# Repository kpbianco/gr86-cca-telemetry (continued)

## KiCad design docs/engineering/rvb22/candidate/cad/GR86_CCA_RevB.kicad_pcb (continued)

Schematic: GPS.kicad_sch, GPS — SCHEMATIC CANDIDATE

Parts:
C401, C402: 22u /25V X7R 10%; C_1210_3225Metric; MPN MCAST32MSB7226KPNA01; LCSC C5372271
C403, C404, C405: 100n /50V X7R; C_0603_1608Metric; MPN GCM188R71H104KA57D; LCSC C85864
D401: SEARCH (blink / no fix); LED_0603_1608Metric; MPN APT1608SGC; LCSC C5875754
D402: TPD1E05U06DPYR; TI_DPY0002A_TPD1E05U06_SMDMask; MPN TPD1E05U06DPYR; LCSC C436349
J401: U.FL-R-SMT-1(80); Hirose_UFL_R_SMT_1_80_RevB; MPN U.FL-R-SMT-1(80); LCSC C88374
L406: 1.6nH 5% RF MATCH; Murata_LQW18AS_1608; MPN LQW18AS1N6J0ZD
R401: 0R GPS ISOLATION; R_0603_1608Metric; MPN CRCW06030000Z0EA; LCSC C844915
R402, R403, R404: 220R; R_0603_1608Metric; MPN AA0603FR-07220RL; LCSC C2100485
R405: 1k; R_0603_1608Metric; MPN CRCW06031K00FKEA; LCSC C844920
R407, R408, R409: 100k; R_0603_1608Metric; MPN CRCW0603100KFKEA; LCSC C844916
R410: 10k /UART idle; R_0603_1608Metric; MPN CRCW060310K0FKEA; LCSC C844918
R411: 100k /off-state; R_0603_1608Metric; MPN CRCW0603100KFKEA; LCSC C844916
TP401: TP_GPS_TX; TestPoint_Pad_D1.5mm; MPN BARE PCB PAD
TP402: TP_GPS_RX; TestPoint_Pad_D1.5mm; MPN BARE PCB PAD
TP403: TP_GPS_PPS; TestPoint_Pad_D1.5mm; MPN BARE PCB PAD
TP404: TP_GPS_3V3; TestPoint_Pad_D1.5mm; MPN BARE PCB PAD
TP405: TP_GPS_GND; TestPoint_Pad_D1.5mm; MPN BARE PCB PAD
U401: PA1616D; CDTop_PA1616D_20Pad_v06; MPN PA1616D
U402, U404: SN74LVC2G125DCUR; VSSOP-8_2.3x2mm_P0.5mm; MPN SN74LVC2G125DCUR; LCSC C21404
U403: MIC5504-3.3YM5-TR; SOT-23-5; MPN MIC5504-3.3YM5-TR; LCSC C88419

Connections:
+3V3: C404.1, R410.1, U402.8 (VCC); also elsewhere on the board
+5V: R401.1; also elsewhere on the board
GND: C401.2, C402.2, C403.2, C404.2, C405.2, D401.1 (K), D402.2 (GND_A), J401.2 (Ext), R407.2, R408.2, R409.2, R411.2, TP405.1, U401.3 (GND), U401.8 (GND), U401.12 (GND), U401.19 (GND), U402.1 (1OE_N), U402.4 (GND), U402.7 (2OE_N), U403.2 (GND), U404.1 (1OE_N), U404.4 (GND), U404.7 (2OE_N); also elsewhere on the board
GPS_3V3: C402.1, C403.1, C405.1, TP404.1, U401.1 (VCC), U403.5 (VOUT), U404.8 (VCC)
GPS_5V_IN: C401.1, R401.2, U403.1 (VIN), U403.3 (EN)
GPS_ANT_RF_BIASED: L406.1, U401.11 (EX_ANT_BIASED)
GPS_EXT_ANT: D402.1 (IO_K), J401.1 (In), L406.2
GPS_FIX_RAW: R409.1, U401.5 (3D_FIX), U404.5 (2A)
GPS_PPS_BUFFER: R403.1, U402.3 (2Y)
GPS_PPS_MCU: R403.2; also elsewhere on the board
GPS_PPS_RAW: R408.1, TP403.1, U401.13 (PPS_2V8), U402.5 (2A)
GPS_RX_BUFFER: R404.1, U404.6 (1Y)
GPS_RX_MODULE: R404.2, TP402.1, U401.10 (RX0)
GPS_SEARCH_BUFFER: R405.1, U404.3 (2Y)
GPS_SEARCH_LED_A: D401.2 (A), R405.2
GPS_TX_BUFFER: R402.1, U402.6 (1Y)
GPS_TX_MCU: R410.2, R411.1, U404.2 (1A); also elsewhere on the board
GPS_TX_MODULE_BUFFERED: R402.2; also elsewhere on the board
GPS_TX_RAW: R407.1, TP401.1, U401.9 (TX0), U402.2 (1A)

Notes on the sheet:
RVB-05 GPS — TX/RX CROSSED; LEVEL BUFFERS; DEDICATED3.3V PA1616D pin1 is upper-left in the manufacturer top view. No electrical pad21.
U402 receives GPS TX/PPS on main3V3; U404 drives GPS RX on GPS3V3. Exact TI input VIH2.0V. R410/R411 set GPIO17 UART idle; GPIO17 may drive LOW briefly at power-up, so firmware renegotiates after boot. GPS-only fixture:1k bleed on main3V3, verify main rail<=0.2V before asserting off-domain behavior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
UART default and external-antenna ESD

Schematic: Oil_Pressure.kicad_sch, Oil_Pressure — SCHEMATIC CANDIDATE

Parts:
C501, C513, C523: 22n /50V X7R; C_0603_1608Metric; MPN CGA3E2X7R1H223K080AE; LCSC C2176922
C502, C531: 100n /50V X7R; C_0603_1608Metric; MPN GCM188R71H104KA57D; LCSC C85864
C503: 100n /100V X7R; C_0805_2012Metric; MPN CGA4J2X7R2A104K125AA; LCSC C342919
C504, C505, C506: 10u /50V X7R; KEMET_C1210_10u50V; MPN C1210C106K5RACTU; LCSC C2167688
C511, C512, C521, C522: 1u /16V X7R; C_0603_1608Metric; MPN GCM188R71C105KA64D; LCSC C161212
C514, C524: 100p /50V C0G5%; C_0603_1608Metric; MPN CGA3E2C0G1H101J080AA; LCSC C76709
C532: 10n /50V C0G 5% OUT HF; C_0603_1608Metric; MPN GRM1885C1H103JA01D
D501: ESD2CAN24DBZRQ1; SOT-23; MPN ESD2CAN24DBZRQ1; LCSC C5736151
D502: SS16 /60V Schottky; D_SMA; MPN SS16HE3_B/H; LCSC C266798
D511, D512, D521, D522: PMEG2010BEA,115; Nexperia_SOD323_PMEG2010BEA; MPN PMEG2010BEA,115; LCSC C455041
R501: 27.4k /0.1%; R_0603_1608Metric; MPN TNPW060327K4BEEA; LCSC C2079063
R502, R504: 10k /0.1%; R_0603_1608Metric; MPN TNPW060310K0BEEA; LCSC C844890
R503: 36.5k /0.1%; R_0603_1608Metric; MPN TNPW060336K5BEEA; LCSC C2089518
R505: 118k /0.1%; R_0805_2012Metric; MPN TNPW0805118KBEEA; LCSC C1709453
R506: 100k; R_0603_1608Metric; MPN CRCW0603100KFKEA; LCSC C844916
R507: 4.7R /1% pulse HP; R_2512_6332Metric; MPN CRCW25124R70FKEGHP; LCSC C2075852
R511, R521: 1M /0.1%; R_0805_2012Metric; MPN TNPW08051M00BEEA; LCSC C844679
R512, R522: 4.02k /0.1%; R_0603_1608Metric; MPN TNPW06034K02BEEA; LCSC C844459
R513, R523: 124k /0.1%; R_0805_2012Metric; MPN TNPW0805124KBEEA; LCSC C1709494
R514, R524: 1k /0.1%; R_0603_1608Metric; MPN TNPW06031K00BEEA; LCSC C844891
R515, R525: 220R /1%150ppm; R_0603_1608Metric; MPN AA0603FR-07220RL; LCSC C2100485
TP501: TP_OIL_SIG; TestPoint_Pad_D1.5mm; MPN BARE PCB PAD
TP502: TP_OIL_FILTERED; TestPoint_Pad_D1.5mm; MPN BARE PCB PAD
TP503: TP_ADC_NODE; TestPoint_Pad_D1.5mm; MPN BARE PCB PAD
TP504: TP_OIL_GND; TestPoint_Pad_D1.5mm; MPN BARE PCB PAD
TP505: TP_OIL_5V; TestPoint_Pad_D1.5mm; MPN BARE PCB PAD
TP506: TP_OIL_EXC_ADC; TestPoint_Pad_D1.5mm; MPN BARE PCB PAD
TP507: TP_OIL_SHDN; TestPoint_Pad_D1.5mm; MPN BARE PCB PAD
TP508: TP_OIL_POWER_FAULT; TestPoint_Pad_D1.5mm; MPN BARE PCB PAD
TP509: TP_OIL_EFUSE_RTN; TestPoint_Pad_D1.5mm; MPN BARE PCB PAD
TP510: TP_OIL_EFUSE_OUT; TestPoint_Pad_D1.5mm; MPN BARE PCB PAD
U501: TPS26600PWPR; TI_PWP0016A_TPS2660; MPN TPS26600PWPR; LCSC C544399
U502: OPA2333AIDR; SOIC-8_3.9x4.9mm_P1.27mm; MPN OPA2333AIDR; LCSC C38732

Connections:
+3V3: C531.1, D511.1 (K), D521.1 (K), R506.1, U502.8 (VPOS); also elsewhere on the board
+5V: C502.1, R501.1, R503.1, U501.1 (IN1), U501.2 (IN2); also elsewhere on the board
ADC_NODE: C513.1, D511.2 (A), D512.1 (K), R513.1, R515.2, TP503.1; also elsewhere on the board
GND: C502.2, C503.2, C504.2, C505.2, C506.2, C511.2, C512.2, C513.2, C521.2, C522.2, C523.2, C531.2, C532.2, D501.3 (GND), D502.2 (A), D512.2 (A), D522.2 (A), R512.2, R514.2, R522.2, R524.2, TP504.1, U501.9 (GND), U502.4 (VNEG); also elsewhere on the board
OIL_5V: C503.1, D501.2 (IO2), R507.2, R521.1, TP505.1; also elsewhere on the board
OIL_AMP_OUT: C514.1, R515.1, U502.1 (OUT_A)
OIL_DVDT: C501.1, U501.12 (DVDT)
OIL_EFUSE_OUT: C504.1, C505.1, C506.1, C532.1, D502.1 (K), R507.1, TP510.1, U501.15 (OUT1), U501.16 (OUT2)
OIL_EFUSE_RTN: C501.2, R502.2, R504.2, R505.2, TP509.1, U501.8 (RTN), U501.17 (EP_RTN)
OIL_EXCITATION_ADC: C523.1, D521.2 (A), D522.1 (K), R523.1, R525.2, TP506.1; also elsewhere on the board
OIL_EXC_AMP_OUT: C524.1, R525.1, U502.7 (OUT_B)
OIL_EXC_FB: C524.2, R523.2, R524.1, U502.6 (INB_N)
OIL_EXC_FILTERED: C521.1, C522.1, R521.2, R522.1, U502.5 (INB_P)
OIL_FB: C514.2, R513.2, R514.1, U502.2 (INA_N)
OIL_FILTERED: C511.1, C512.1, R511.2, R512.1, TP502.1, U502.3 (INA_P)
OIL_ILIM: R505.1, U501.11 (ILIM)
OIL_OVP: R503.2, R504.1, U501.5 (OVP)
OIL_POWER_FAULT_N: R506.2, TP508.1, U501.14 (FLT_N)
OIL_SHDN: TP507.1, U501.7 (SHDN)
OIL_SIG: D501.1 (IO1), R511.1, TP501.1; also elsewhere on the board
OIL_UVLO: R501.2, R502.1, U501.3 (UVLO)

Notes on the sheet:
RVB-06 — HONEYWELL150psi /RATIOMETRIC5V /GPIO1 ADC Connector signal → 1:249.76 attenuator → precision gain125 → low-impedance ADC drive. OIL5V excitation is current limited and reverse-current blocked; no direct5V-to-ADC path.
RTN is a private eFuse reference; do not short it to GND. Its thermal pad also goes to RTN. MODE floats for circuit-breaker/auto-retry. SHDN uses its internal2–3.4V pullup; TP permits temporary low-to-RTN reset. UVLO is externally programmed: grounding it would select a14.9V default and disable a5V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
RVB22 C532 OUT-to-GND HF bypass:10nF C0G50V; never privateRTN. Direct U501 OUTpad16 feed also joins C504 OUTland and existing In1 OUTcopper; use actual non-tree nodal model. Preserve C504/C505/C506 bulk and C514 feedback. New-loop25nH/common-star10nH are allocations; native fill and hardware remain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

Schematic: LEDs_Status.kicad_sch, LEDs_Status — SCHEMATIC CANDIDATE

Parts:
D601: PWR; LED_0603_1608Metric; MPN APT1608SGC; LCSC C5875754
D602: BLE; LED_0603_1608Metric; MPN APT1608SGC; LCSC C5875754
D603: CAN; LED_0603_1608Metric; MPN APT1608SGC; LCSC C5875754
D604: GPS; LED_0603_1608Metric; MPN APT1608SGC; LCSC C5875754
D605: SYS; LED_0603_1608Metric; MPN APT1608SGC; LCSC C5875754
D606: OIL; LED_0603_1608Metric; MPN APT1608SGC; LCSC C5875754
R601: 1k / GPIO15; R_0603_1608Metric; MPN CRCW06031K00FKEA; LCSC C844920
R602: 1k / GPIO6; R_0603_1608Metric; MPN CRCW06031K00FKEA; LCSC C844920
R603: 1k / GPIO7; R_0603_1608Metric; MPN CRCW06031K00FKEA; LCSC C844920
R604: 1k / GPIO8; R_0603_1608Metric; MPN CRCW06031K00FKEA; LCSC C844920
R605: 1k / GPIO10; R_0603_1608Metric; MPN CRCW06031K00FKEA; LCSC C844920
R606: 1k / GPIO9; R_0603_1608Metric; MPN CRCW06031K00FKEA; LCSC C844920

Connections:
GND: D601.1 (K), D602.1 (K), D603.1 (K), D604.1 (K), D605.1 (K), D606.1 (K); also elsewhere on the board
LED_BLE: R602.1; also elsewhere on the board
LED_BLE_A: D602.2 (A), R602.2
LED_CAN: R603.1; also elsewhere on the board
LED_CAN_A: D603.2 (A), R603.2
LED_GPS: R604.1; also elsewhere on the board
LED_GPS_A: D604.2 (A), R604.2
LED_OIL: R606.1; also elsewhere on the board
LED_OIL_A: D606.2 (A), R606.2
LED_PWR: R601.1; also elsewhere on the board
LED_PWR_A: D601.2 (A), R601.2
LED_SYS: R605.1; also elsewhere on the board
LED_SYS_A: D605.2 (A), R605.2

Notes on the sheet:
STATUS INDICATORS — ACTIVE HIGH GPIO3/GPIO46 strapping pins are free of external LED loads in Rev B. Firmware Rev B contract moves OIL to GPIO9 and PWR to GPIO15.
1000ohm current limiting. See qualification/LED_STRAP_REVIEW.md. Indicators represent firmware state and do not replace physical rail/bus measurements.

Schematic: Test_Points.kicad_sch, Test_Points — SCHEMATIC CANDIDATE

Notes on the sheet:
TEST AND ISOLATION DIRECTORY Probe points are placed on the functional sheets beside their circuits. Bring-up removes rail0ohm links before testing each source independently. R301 TXD and R306 termination are DNP; SJ301 is open for vehicle tap use. L406 RF matching inductor is factory fitted in RVB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

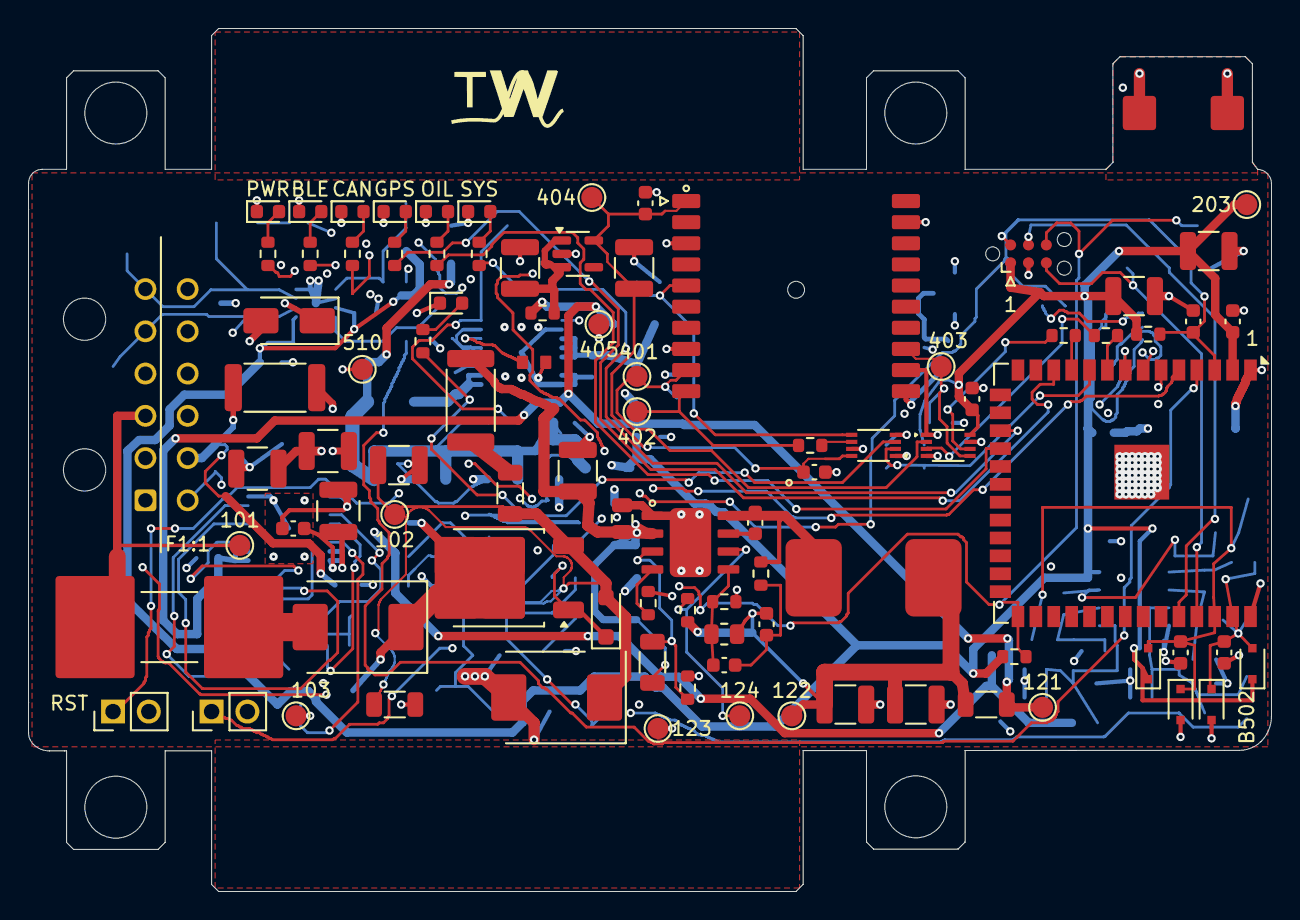
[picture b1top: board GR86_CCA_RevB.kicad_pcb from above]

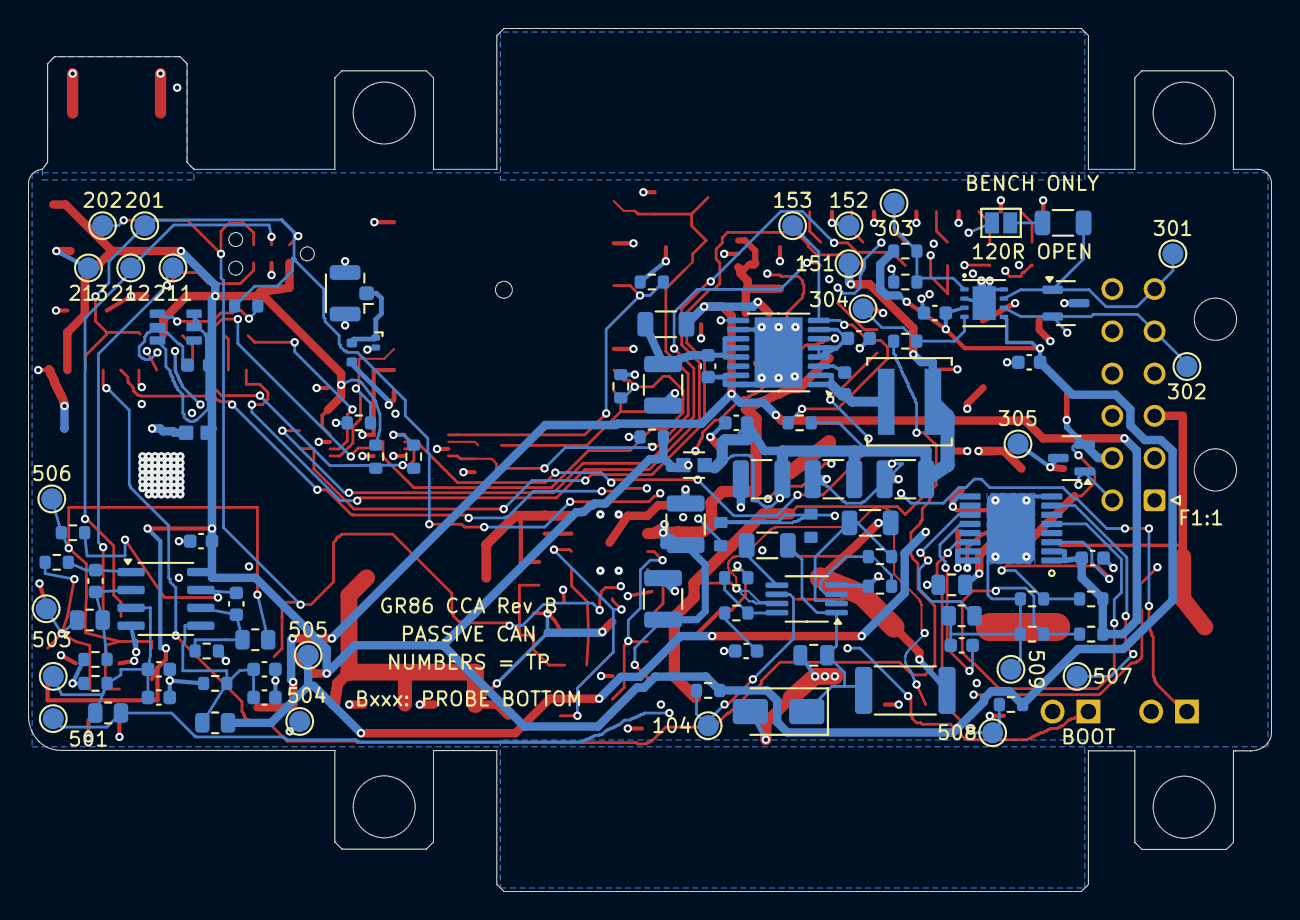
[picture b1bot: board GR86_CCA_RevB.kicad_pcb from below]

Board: 4 copper layers, 88.3 x 61.3 mm, 199 parts (103 on the bottom side), 92 nets.

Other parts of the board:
MH901, MH902, MH903, MH904: 4.4mm NPTH; MountingHole_4.4mm_Outboard

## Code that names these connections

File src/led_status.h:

#pragma once

#include <stdint.h>

#ifndef LED_PWR_GPIO
#define LED_PWR_GPIO 15
#endif

#ifndef LED_PWR_ACTIVE_LOW
#define LED_PWR_ACTIVE_LOW 0
#endif

#ifndef LED_BLE_GPIO
#define LED_BLE_GPIO 6
#endif

#ifndef LED_BLE_ACTIVE_LOW
#define LED_BLE_ACTIVE_LOW 0
#endif

#ifndef LED_CAN_GPIO
#define LED_CAN_GPIO 7
#endif

#ifndef LED_CAN_ACTIVE_LOW
#define LED_CAN_ACTIVE_LOW 0
#endif

#ifndef LED_GPS_GPIO
#define LED_GPS_GPIO 8
#endif

#ifndef LED_GPS_ACTIVE_LOW
#define LED_GPS_ACTIVE_LOW 0
#endif

#ifndef LED_SYS_GPIO
#define LED_SYS_GPIO 10
#endif

#ifndef LED_SYS_ACTIVE_LOW
#define LED_SYS_ACTIVE_LOW 0
#endif

#ifndef LED_OIL_GPIO
#define LED_OIL_GPIO 3
#endif

#ifndef LED_OIL_ACTIVE_LOW
#define LED_OIL_ACTIVE_LOW 0
#endif

enum class LedPattern : uint8_t {
  Off = 0,
  Solid,
  BlinkFast,
  BlinkSlow,
  Pulse2Every2s,
  Pulse3Every2s,
};

void led_init();

void led_set_power(LedPattern pattern);
void led_set_ble(LedPattern pattern);
void led_set_can(LedPattern pattern);
void led_set_gps(LedPattern pattern);
void led_set_sys(LedPattern pattern);
void led_set_oil(LedPattern pattern);

void led_service(uint32_t now_ms);

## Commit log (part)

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2025-10-15 libs
2025-10-15 Add NVS-backed config persistence and custom divider storage
2025-10-15 Refine SHOW CLI output
2025-10-15 Add firmware version metadata to boot and stats
2025-10-15 Add periodic diagnostic CAN-over-BLE frame
2025-10-15 Add TWAI bus-off recovery helper
2025-10-15 Add task watchdog feeding for ESP32 loop
2025-10-15 Add RaceChrono preset documentation
2025-10-15 Implement BLE TX governor
2025-10-15 Improve BLE reconnect robustness and CLI safety
2025-10-15 Fix forward declarations for governor snapshot
2025-10-17 Add GPS telemetry streaming
2025-10-17 Add RaceChrono GPS fallback handling
2025-10-17 Simplify GPS BLE integration to avoid boot loop
2025-10-17 Fix GPS BLE characteristic lookup
2025-10-17 Stabilize RaceChrono GPS characteristic discovery
2025-10-18 Fix RaceChrono filter handling for CAN allow list
2025-10-18 Fix RaceChrono 11-bit CAN allow parsing
2025-10-18 Fix RaceChrono allow PID interval parsing
2025-10-18 Handle big-endian RaceChrono allow IDs
2025-10-18 Decode RaceChrono interval hints as little-endian
2025-10-18 Enable task watchdog and log reset reason
2025-10-18 Implement per-PID allow-all throttle
2025-10-18 Remove allow-all throttle gating
2025-10-18 Ensure sniff-all PIDs get divider entries
2025-10-19 Remove allow-all throttle gate
2025-10-19 Fix watchdog init for ESP-IDF 5.x
2025-10-31 Add TWAI error telemetry and auto-recovery
2025-10-31 Fix ESP-IDF v5 build issues for TWAI telemetry
2025-10-31 Improve GPS detection fallback and CAN diagnostics
2025-10-31 Stabilize GPS fallback handling
2025-10-31 Make GPS bring-up non-blocking
2025-10-31 Fix GPS fractional second parsing
2025-10-31 Stabilize GPS monotonic timebase
2025-11-03 Add BLE link priority controls
2025-11-03 Forward declare PidExtra for Arduino prototypes
2025-11-03 Expand default CAN allow list for RaceChrono
2025-11-03 Refactor CAN profile into selectable pid map
2025-11-03 Fix PID map include guard
2025-11-03 Tighten PID map extra creation
2025-11-03 Qualify PID map type references
2025-11-03 Ensure CAN updates are sent on value changes
2025-11-03 Handle RaceChrono filter commands without dropping CAN PIDs
2025-11-03 Declare resetSkippedUpdatesCounters before FIL handler
2025-11-03 Improve CAN RX buffering throughput
2025-11-03 Balance CAN RX polling with GPS servicing
2025-11-04 Ensure GPS notifications use fresh timestamps
2025-11-04 Add CAN BLE notify guard
2025-11-04 Harden NMEA parsing and add tests
2025-11-04 Make GPS NMEA parser header-only for Arduino
2025-11-04 Move GPS NMEA parser into Arduino library
2025-11-04 Place GPS parser sources under Arduino src layout
2025-11-04 Add scheduler helper for periodic tasks
2025-11-04 Handle oil ADC glitches and persist calibration blob
2025-11-05 Secure FIL writes with token auth and rate limiting
2025-11-05 Fix FIL characteristic encryption configuration
2025-11-05 Add OTA update support with signature verification
2025-11-05 Add CAN RX timestamping and BLE timing diagnostics
2025-11-06 Fix NimBLE diag characteristic handling
2025-11-06 Add OTA update helpers and fix ESP-IDF 5 build issues
2025-11-06 Add CAN RX timestamp diagnostics stream
2025-11-06 Add GPS PPS discipline for monotonic time
2025-11-06 Fix GPS PPS globals scope for ISR
2025-11-11 Add supervisor to catch subsystem starvation
2025-11-11 Add heap and queue telemetry to CAN diagnostics
2025-11-11 Fix NimBLE watermark helper definition
2025-11-11 Add profile-based TWAI filter configuration
2025-11-11 Fix TWAI filter helpers for Arduino compile
2025-11-11 Force dual TWAI filters for profile builds
2025-11-11 Improve CAN RX validation and buffering
2025-11-11 Add status LED manager and integrate runtime signals
2025-11-11 Add oil status LED and improve LED servicing
2025-11-11 Improve LED servicing and defaults
2025-11-11 Improve LED refresh for BLE and GPS
2025-11-11 Adjust LED patterns and reset behavior
2025-11-11 Fix LED polarity defaults and validate GPIOs
2025-11-11 Make status LEDs responsive without BLE connection
2025-11-11 Improve GPS baud negotiation reliability
2025-11-12 Refine BLE notify failure metrics
2025-11-12 Fix governor snapshot constant placement
2025-11-12 Reduce disconnect churn and noisy logs
2025-11-12 Improve CAN inactivity handling
2025-11-18 Document firmware layout and reorganize repo
2025-11-18 Add release-ready summary to README
